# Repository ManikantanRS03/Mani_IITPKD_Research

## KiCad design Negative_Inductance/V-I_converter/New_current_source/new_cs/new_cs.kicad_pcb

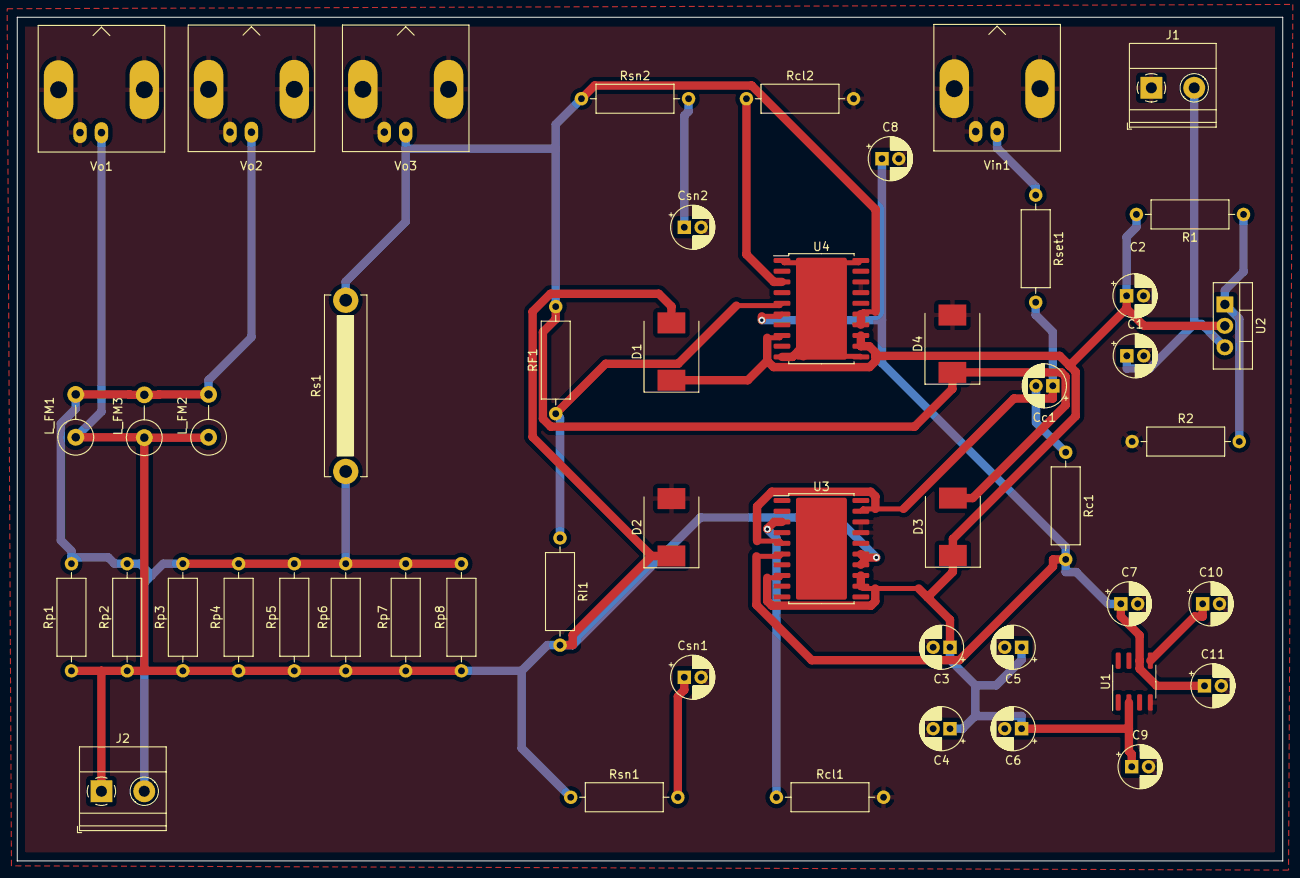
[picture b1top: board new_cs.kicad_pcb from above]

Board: 2 copper layers, 150.0 x 100.0 mm, 50 parts (0 on the bottom side), 17 nets.

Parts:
C1, C2, C4, C6, C11: 47uF; CP_Radial_D5.0mm_P2.00mm
C3, C5, C7, C8: 0.1uF; CP_Radial_D5.0mm_P2.00mm
C9, C10: 1uF; CP_Radial_D5.0mm_P2.00mm
Cc1: 0.47uF; CP_Radial_D5.0mm_P2.00mm
Csn1, Csn2: 0.01uF; CP_Radial_D5.0mm_P2.00mm
D1, D2, D3, D4: 0.35V; D_SMC
J1: +10V; TerminalBlock_Phoenix_MKDS-1,5-2-5.08_1x02_P5.08mm_Horizont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
J2: Iout; TerminalBlock_Phoenix_MKDS-1,5-2-5.08_1x02_P5.08mm_Horizont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
L_FM1, L_FM2, L_FM3: 0.1mH; L_Axial_L9.5mm_D4.0mm_P5.08mm_Vertical_Fastron_SMCC
R1: 240; R_Axial_DIN0309_L9.0mm_D3.2mm_P12.70mm_Horizontal
R2: 720; R_Axial_DIN0309_L9.0mm_D3.2mm_P12.70mm_Horizontal
RF1: 1k; R_Axial_DIN0309_L9.0mm_D3.2mm_P12.70mm_Horizontal
RI1: 1k; R_Axial_DIN0309_L9.0mm_D3.2mm_P12.70mm_Horizontal
Rc1: 249; R_Axial_DIN0309_L9.0mm_D3.2mm_P12.70mm_Horizontal
Rcl1, Rcl2: 5.49k; R_Axial_DIN0309_L9.0mm_D3.2mm_P12.70mm_Horizontal
Rp1, Rp2, Rp3, Rp4, Rp5, Rp6, Rp7, Rp8: 1; R_Axial_DIN0309_L9.0mm_D3.2mm_P12.70mm_Horizontal
Rs1: 4; R_Bare_Metal_Element_L21.3mm_W4.8mm_P20.30mm
Rset1: 475; R_Axial_DIN0309_L9.0mm_D3.2mm_P12.70mm_Horizontal
Rsn1, Rsn2: 10; R_Axial_DIN0309_L9.0mm_D3.2mm_P12.70mm_Horizontal
U1: REF5025AD; SOIC-8_3.9x4.9mm_P1.27mm
U2: LM317_TO-220; TO-220-3_Vertical
U3, U4: OPA569DWP; SO-20-1EP_7.52x12.825mm_P1.27mm_EP6.045x12.09mm_Mask3.56x4.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
Vin1: Input; BNC_Amphenol_B6252HB-NPP3G-50_Horizontal
Vo1, Vo2, Vo3: Output; BNC_Amphenol_B6252HB-NPP3G-50_Horizontal

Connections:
GND: C1.2, C2.2, C3.2, C4.2, C5.2, C6.2, C7.2, C8.2, C9.2, C10.2, C11.2, Csn1.2, Csn2.2, D2.2 (A), D4.2 (A), J1.1, R2.1, Rcl1.2, Rcl2.2, U1.4 (GND), U3.1 (PAD), U3.10 (PAD), U3.11 (PAD), U3.17 (V-), U3.18 (V-), U3.20 (PAD), U3.21 (PAD), U4.17 (V-), U4.18 (V-), Vin1.2 (Ext), Vo1.2 (Ext), Vo2.2 (Ext), Vo3.2 (Ext)
Imon: Cc1.1, Rset1.2, U3.5 (-IN), U3.19 (IMON)
unnamed: C1.1, J1.2, U2.3 (VI)
unnamed: C10.1, U1.5 (Trim/NR)
unnamed: Cc1.2, Rc1.1
unnamed: Csn1.1, Rsn1.2
unnamed: Csn2.1, Rsn2.2
unnamed: R1.1, R2.2, U2.1 (ADJ)
unnamed: Rcl1.1, U3.3 (ISET)
unnamed: Rcl2.1, U4.3 (ISET)
unnamed: Rset1.1, Vin1.1 (In)
unnamed: U4.1 (PAD), U4.10 (PAD), U4.11 (PAD), U4.20 (PAD), U4.21 (PAD)
Vcc: C2.1, C3.1, C4.1, C5.1, C6.1, C9.1, D1.1 (K), D3.1 (K), R1.2, U1.2 (Vin), U2.2 (VO), U3.8 (ENA), U3.12 (V+), U3.13 (V+), U4.8 (ENA), U4.12 (V+), U4.13 (V+)
Vm1: D1.2 (A), D2.1 (K), J2.1, L_FM1.1, L_FM2.1, L_FM3.1, RI1.2, Rp1.1, Rp2.1, Rp3.1, Rp4.1, Rp5.1, Rp6.1, Rp7.1, Rp8.1, Rsn1.1, U3.14 (OUT), U3.15 (OUT), Vo1.1 (In)
Vm2: J2.2, L_FM1.2, L_FM2.2, L_FM3.2, Rp1.2, Rp2.2, Rp3.2, Rp4.2, Rp5.2, Rp6.2, Rp7.2, Rp8.2, Rs1.1, Vo2.1 (In)
Vm3: D3.2 (A), D4.1 (K), RF1.2, Rs1.2, Rsn2.1, U4.14 (OUT), U4.15 (OUT), Vo3.1 (In)
Vref: C7.1, C8.1, C11.1, Rc1.2, U1.6 (Vout), U3.6 (+IN), U4.6 (+IN)

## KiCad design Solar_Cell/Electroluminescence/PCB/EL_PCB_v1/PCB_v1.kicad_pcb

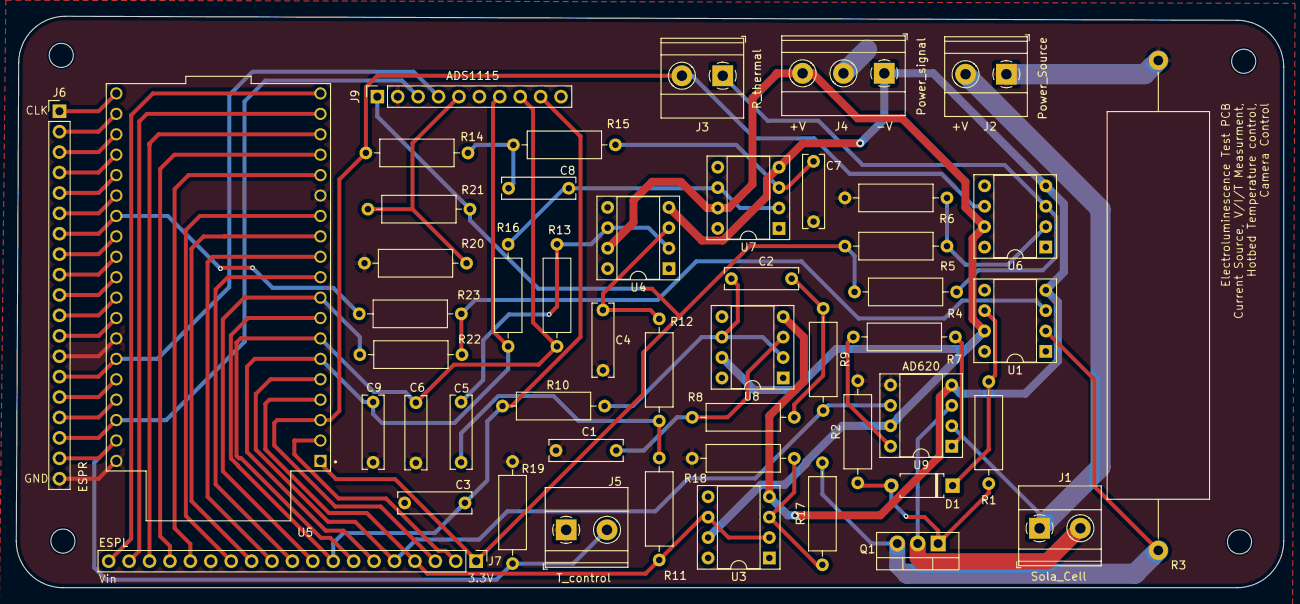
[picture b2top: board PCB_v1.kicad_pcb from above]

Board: 2 copper layers, 157.7 x 71.1 mm, 54 parts (0 on the bottom side), 59 nets.

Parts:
C1, C2, C3, C4, C5, C6, C7, C8, C9: C; C_Rect_L9.0mm_W2.5mm_P7.50mm_MKT
D1: D; D_A-405_P7.62mm_Horizontal
H1, H2, H3, H4: MountingHole; MountingHole_3mm
J1: Sola_Cell; TerminalBlock_Phoenix_MKDS-1,5-2-5.08_1x02_P5.08mm_Horizont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
J2: Power_Source; TerminalBlock_Phoenix_MKDS-1,5-2-5.08_1x02_P5.08mm_Horizont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
J3: R_thermal; TerminalBlock_Phoenix_MKDS-1,5-2-5.08_1x02_P5.08mm_Horizont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
J4: Power_signal; TerminalBlock_Phoenix_MKDS-1,5-3-5.08_1x03_P5.08mm_Horizont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
J5: T_control; TerminalBlock_Phoenix_MKDS-1,5-2-5.08_1x02_P5.08mm_Horizont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
J6: ESPR; PinHeader_1x19_P2.54mm_Vertical
J7: ESPL; PinHeader_1x19_P2.54mm_Vertical
J9: ADS1115; PinSocket_1x10_P2.54mm_Vertical
Q1: IRF540N; TO-220-3_Vertical
R1, R2, R4, R5, R6, R7, R8, R9, R10, R11, R12, R13, R14, R15, R16, R17, R18, R19, R20, R21, R22, R23: R_US; R_Axial_DIN0309_L9.0mm_D3.2mm_P12.70mm_Horizontal
R3: R_US; R_Axial_Power_L48.0mm_W12.5mm_P60.96mm
U1, U3, U4, U6, U7, U8: OP07; DIP-8_W7.62mm_Socket
U5: DEVKIT_V1_ESP32-WROOM-32; MODULE_DEVKIT_V1_ESP32-WROOM-32
U9: AD620; DIP-8_W7.62mm_Socket

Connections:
3.3V: J7.1, J9.1, R4.2, R5.2, R21.2, U5.1 (3V3)
A0: C9.1, J7.6, J9.7, R16.1, U5.6 (IO35)
A1: C6.1, J7.7, J9.8, R13.1, U5.7 (IO32)
A2: C3.1, J7.8, J9.9, R10.1, U5.8 (IO33)
ADDR: J9.5, R20.1, R21.1
DAC1: J7.9, R22.2, U5.9 (IO25)
DAC2: J7.10, U5.10 (IO26)
EN: J7.2, U5.2 (EN)
GND: C1.2, C3.2, C4.2, C6.2, C7.2, C9.2, J2.1, J4.2, J5.1, J6.13, J6.19, J7.14, J9.2, R2.2, R3.2, R6.2, R18.2, R19.2, R20.2, U5.14 (GND1), U5.32 (GND2), U5.38 (GND3), U9.5 (Ref)
GPIO0/ADC11: J6.6, U5.25 (IO0)
GPIO2/ADC12: J6.5, U5.24 (IO2)
GPIO4/ADC10: J6.7, R23.2, U5.26 (IO4)
GPIO5: J6.10, U5.29 (IO5)
GPIO6: J6.1, U5.20 (CLK)
GPIO7: J6.2, U5.21 (SD0)
GPIO8: J6.3, U5.22 (SD1)
GPIO9: J7.16, U5.16 (SD2)
GPIO10: J7.17, U5.17 (SD3)
GPIO11: J7.18, U5.18 (CMD)
GPIO12/ADC15: J7.13, U5.13 (IO12)
GPIO13/ADC14: J7.15, U5.15 (IO13)
GPIO14/ADC16: J7.12, U5.12 (IO14)
GPIO15/ADC13: J6.4, U5.23 (IO15)
GPIO16: J6.8, U5.27 (IO16)
GPIO17: J6.9, U5.28 (IO17)
GPIO18: J6.11, U5.30 (IO18)
GPIO19: J6.12, U5.31 (IO19)
GPIO21: J6.14, J9.4, U5.33 (IO21)
GPIO22: J6.17, J9.3, U5.36 (IO22)
GPIO23: J5.2, J6.18, R19.1, U5.37 (IO23)
GPIO27/ADC17: J7.11, U5.11 (IO27)
GPIO34/ADC6: J7.5, R9.2, U5.5 (IO34), U9.6
GPIO36/ADC0: J3.2, J7.3, R14.2, U5.3 (SENSOR_VP), U6.6
GPIO39/ADC3: J7.4, R11.2, U3.2 (-), U3.6, U5.4 (SENSOR_VN)
I_meas: Q1.3 (S), R3.1, R17.2, U1.2 (-)
I_ref: R22.1, R23.1, U1.3 (+)
unnamed: C2.2, R8.2, R9.1
unnamed: C5.2, R11.1, R12.2
unnamed: C8.2, R14.1, R15.2
unnamed: D1.2 (A), Q1.1 (G), R1.1, R2.1
unnamed: D1.1 (K), R1.2, U1.6
unnamed: R7.1, U9.1 (Rg)
unnamed: R7.2, U9.8 (Rg)
unnamed: R17.1, R18.1, U3.3 (+)
unnamed: C4.1, R12.1, U4.3 (+)
unnamed: C5.1, R13.2, U4.2 (-), U4.6
unnamed: R5.1, R6.1, U6.2 (-)
unnamed: C7.1, R15.1, U7.3 (+)
unnamed: C8.1, R16.2, U7.2 (-), U7.6
unnamed: C1.1, R8.1, U8.3 (+)
unnamed: C2.1, R10.2, U8.2 (-), U8.6
R_T1: J3.1, R4.1, U6.3 (+)
Rx0: J6.15, U5.34 (RXD0)
Tx0: J6.16, U5.35 (TXD0)
VEE: J4.1, U1.4 (V-), U3.4 (V-), U4.4 (V-), U6.4 (V-), U7.4 (V-), U8.4 (V-), U9.4 (Vs-)
VSS: J4.3, U1.7 (V+), U3.7 (V+), U4.7 (V+), U6.7 (V+), U7.7 (V+), U8.7 (V+), U9.7 (Vs+)
V_cell+: J1.1, J2.2, U9.2 (-)
V_cell-: J1.2, Q1.2 (D), U9.3 (+)
Vin: J7.19, U5.19 (EXT_5V)

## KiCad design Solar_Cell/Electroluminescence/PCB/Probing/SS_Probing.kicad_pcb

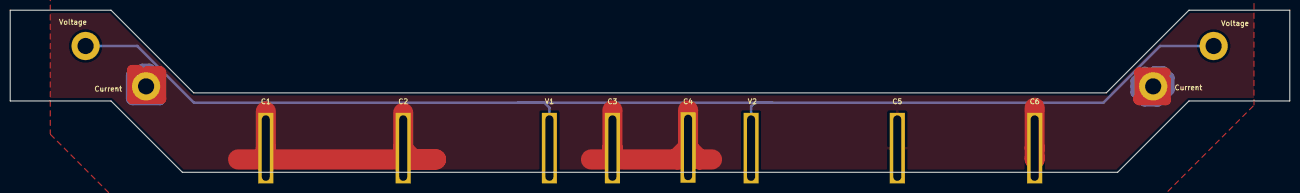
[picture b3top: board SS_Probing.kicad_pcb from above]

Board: 2 copper layers, 253.8 x 32.1 mm, 12 parts (0 on the bottom side), 2 nets.

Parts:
C1, C2, C3, C4, C5, C6: 0.64mm Pogo Pin
Current: Conn_01x02_Socket; MountingHole_3.2mm_M3_DIN965_Pad
Current#2: Conn_01x02_Socket; MountingHole_3.2mm_M3_DIN965_Pad
V1, V2: 0.64mm Pogo Pin
Voltage: Conn_01x02_Socket; MountingHole_3.2mm_M3_DIN965_Pad
Voltage#2: Conn_01x02_Socket; MountingHole_3.2mm_M3_DIN965_Pad

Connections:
Current: C1.1, C2.1, C3.1, C5.1, C6.1, Current.1, Current#2.1, V2.1
Voltage: C4.1, V1.1, Voltage.1, Voltage#2.1

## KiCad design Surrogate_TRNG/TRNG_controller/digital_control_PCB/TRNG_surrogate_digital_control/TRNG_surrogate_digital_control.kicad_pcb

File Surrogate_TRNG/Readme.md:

-> Spice_python_simulation
    . Contains simulation of the surrogate circuit automated through a Python script to generate:
        - Kramers time plots
        - TRNG plots

-> TRNG_controller
    . Contains the BTP work carried out in Sem 7/8. Modified the surrogate circuit to incorporate a        
    digital control mechanism (details of implementation in the report provided)
        - PCB design (KiCad)
        - Measurements done on the setup (more details in the README inside)
        - Noise generation code for the Innovation Lab function generator
        - MATLAB/Simulink simulations to test the control design

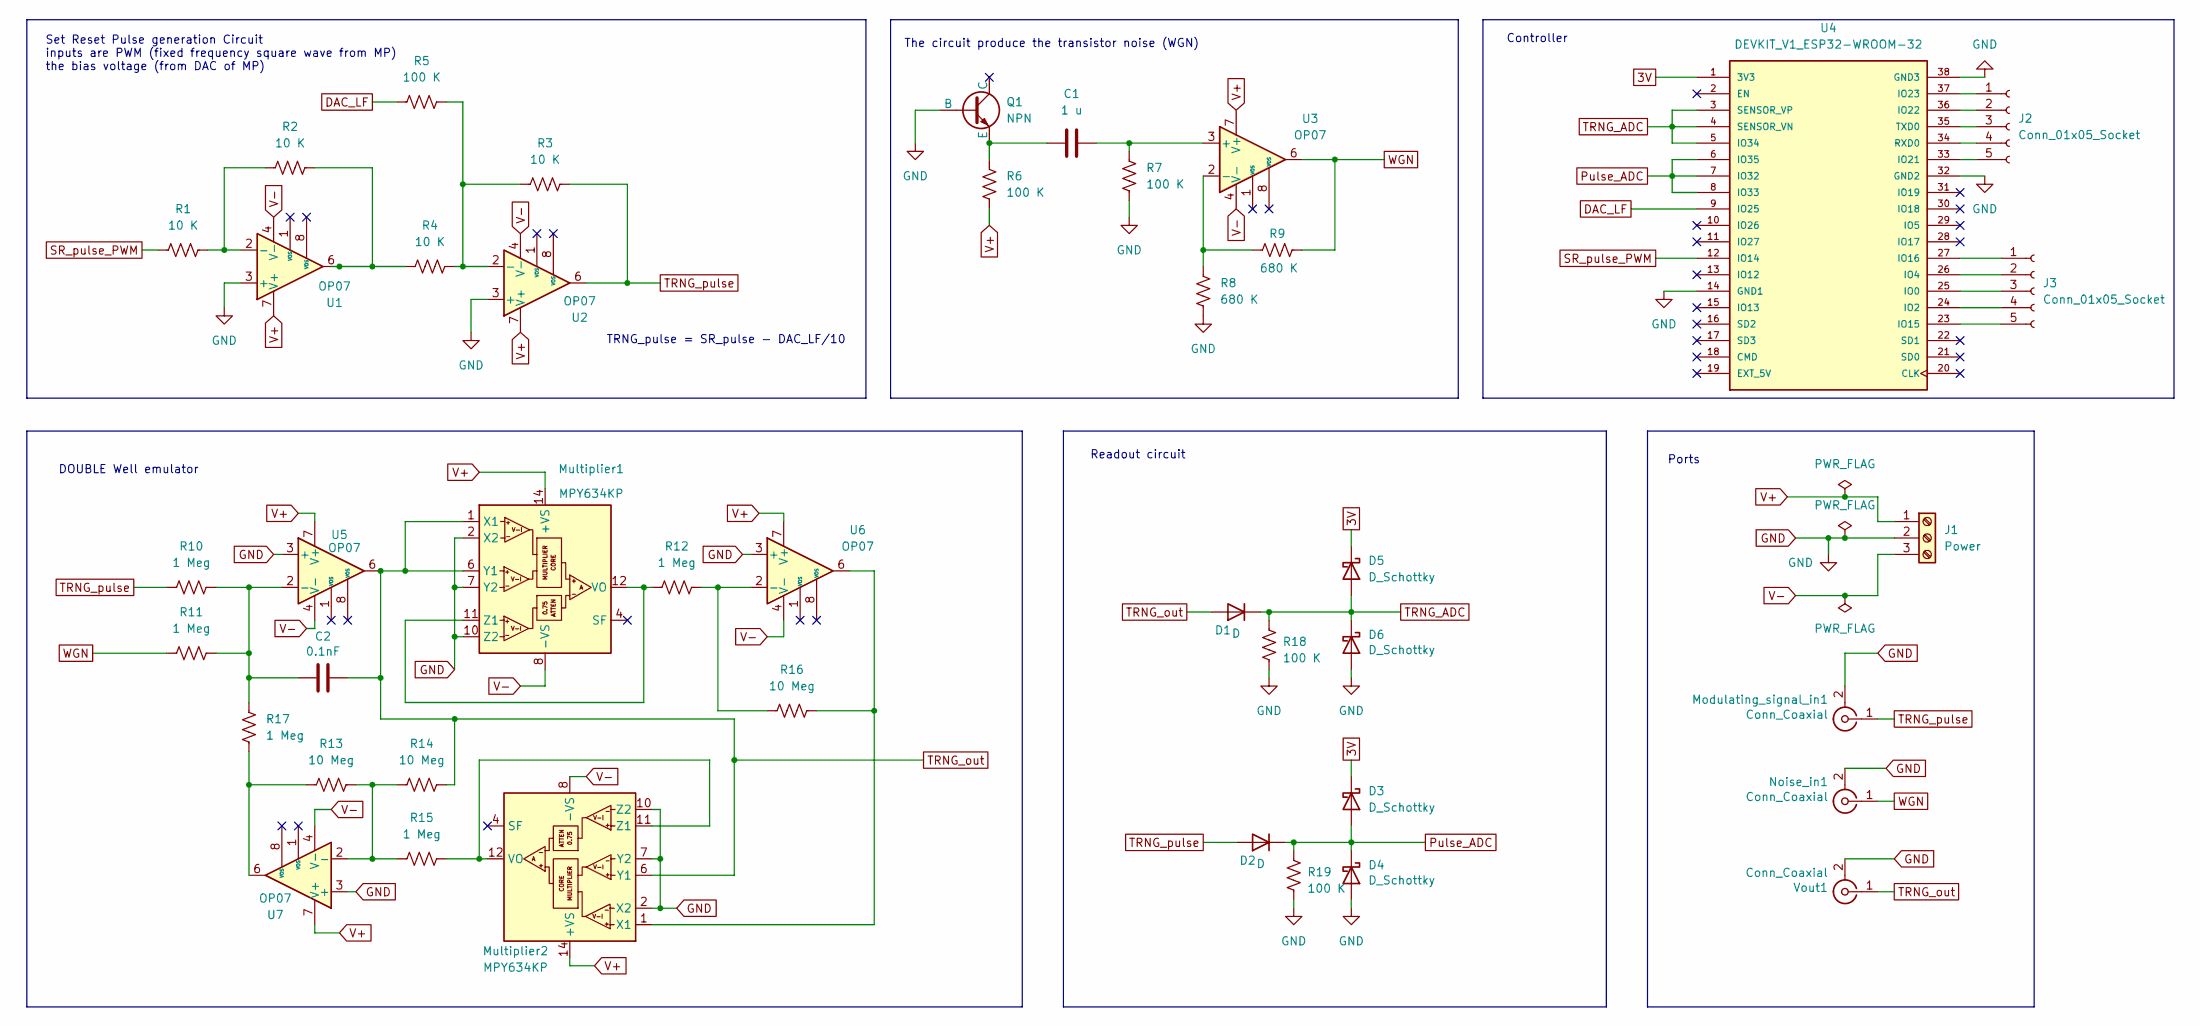
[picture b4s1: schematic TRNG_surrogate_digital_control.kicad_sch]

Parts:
C1: 1 u; C_Rect_L9.0mm_W2.5mm_P7.50mm_MKT
C2: 0.1nF; C_Rect_L9.0mm_W2.5mm_P7.50mm_MKT
D1, D2: D; D_A-405_P7.62mm_Horizontal
D3, D4, D5, D6: D_Schottky; D_A-405_P7.62mm_Horizontal
J1: Power; TerminalBlock_Phoenix_MKDS-3-3-5.08_1x03_P5.08mm_Horizontal
J2, J3: Conn_01x05_Socket; PinSocket_1x05_P2.54mm_Vertical
Modulating_signal_in1: Conn_Coaxial; BNC_Amphenol_B6252HB-NPP3G-50_Horizontal
Multiplier1, Multiplier2: MPY634KP; DIP-14_W7.62mm_Socket
Noise_in1: Conn_Coaxial; BNC_Amphenol_B6252HB-NPP3G-50_Horizontal
Q1: NPN; TO-92
R1, R2, R3, R4: 10 K; R_Axial_DIN0309_L9.0mm_D3.2mm_P12.70mm_Horizontal
R5, R6, R7, R18, R19: 100 K; R_Axial_DIN0309_L9.0mm_D3.2mm_P12.70mm_Horizontal
R8, R9: 680 K; R_Axial_DIN0309_L9.0mm_D3.2mm_P12.70mm_Horizontal
R10, R11, R12, R15, R17: 1 Meg; R_Axial_DIN0309_L9.0mm_D3.2mm_P12.70mm_Horizontal
R13, R14, R16: 10 Meg; R_Axial_DIN0309_L9.0mm_D3.2mm_P12.70mm_Horizontal
U1, U2, U3, U5, U6, U7: OP07; DIP-8_W7.62mm_Socket
U4: DEVKIT_V1_ESP32-WROOM-32; MODULE_DEVKIT_V1_ESP32-WROOM-32; PARTREV N/A
Vout1: Conn_Coaxial; BNC_Amphenol_B6252HB-NPP3G-50_Horizontal

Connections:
3V: D3.1 (K), D5.1 (K), U4.1 (3V3)
DAC_LF: R5.1, U4.9 (IO25)
GND: D4.2 (A), D6.2 (A), J1.2, Modulating_signal_in1.2 (Ext), Multiplier1.2 (X2), Multiplier1.7 (Y2), Multiplier1.10 (Z2), Multiplier2.2 (X2), Multiplier2.7 (Y2), Multiplier2.10 (Z2), Noise_in1.2 (Ext), Q1.2 (B), R7.1, R8.1, R18.1, R19.1, U1.3 (+), U2.3 (+), U4.14 (GND1), U4.32 (GND2), U4.38 (GND3), U5.3 (+), U6.3 (+), U7.3 (+), Vout1.2 (Ext)
unnamed: J2.1, U4.37 (IO23)
unnamed: J2.2, U4.36 (IO22)
unnamed: J2.3, U4.35 (TXD0)
unnamed: J2.4, U4.34 (RXD0)
unnamed: J2.5, U4.33 (IO21)
unnamed: J3.1, U4.27 (IO16)
unnamed: J3.2, U4.26 (IO4)
unnamed: J3.3, U4.25 (IO0)
unnamed: J3.4, U4.24 (IO2)
unnamed: J3.5, U4.23 (IO15)
unnamed: Multiplier1.11 (Z1), Multiplier1.12 (VO), R12.1
unnamed: Multiplier2.11 (Z1), Multiplier2.12 (VO), R15.2
unnamed: Multiplier2.1 (X1), R16.2, U6.6
unnamed: C1.1, Q1.3 (E), R6.2
unnamed: R2.2, R4.1, U1.6
unnamed: R13.1, R17.1, U7.6
unnamed: R1.2, R2.1, U1.2 (-)
unnamed: R3.1, R4.2, R5.2, U2.2 (-)
unnamed: C1.2, R7.2, U3.3 (+)
unnamed: R8.2, R9.2, U3.2 (-)
unnamed: C2.2, R10.2, R11.2, R17.2, U5.2 (-)
unnamed: R12.2, R16.1, U6.2 (-)
unnamed: R13.2, R14.1, R15.1, U7.2 (-)
Pulse_ADC: D2.1 (K), D3.2 (A), D4.1 (K), R19.2, U4.6 (IO35), U4.7 (IO32), U4.8 (IO33)
SR_pulse_PWM: R1.1, U4.12 (IO14)
TRNG_ADC: D1.1 (K), D5.2 (A), D6.1 (K), R18.2, U4.3 (SENSOR_VP), U4.4 (SENSOR_VN), U4.5 (IO34)
TRNG_out: C2.1, D1.2 (A), Multiplier1.1 (X1), Multiplier1.6 (Y1), Multiplier2.6 (Y1), R14.2, U5.6, Vout1.1 (In)
TRNG_pulse: D2.2 (A), Modulating_signal_in1.1 (In), R3.2, R10.1, U2.6
V+: J1.1, Multiplier1.14 (+VS), Multiplier2.14 (+VS), R6.1, U1.7 (V+), U2.7 (V+), U3.7 (V+), U5.7 (V+), U6.7 (V+), U7.7 (V+)
V-: J1.3, Multiplier1.8 (-VS), Multiplier2.8 (-VS), U1.4 (V-), U2.4 (V-), U3.4 (V-), U5.4 (V-), U6.4 (V-), U7.4 (V-)
WGN: Noise_in1.1 (In), R9.1, R11.1, U3.6

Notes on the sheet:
DOUBLE Well emulator
Set Reset Pulse generation Circuit inputs are PWM (fixed frequency square wave from MP) the bias voltage (from DAC of MP)
Ports
Readout circuit
TRNG_pulse = SR_pulse - DAC_LF/10
Controller
The circuit produce the transistor noise (WGN)

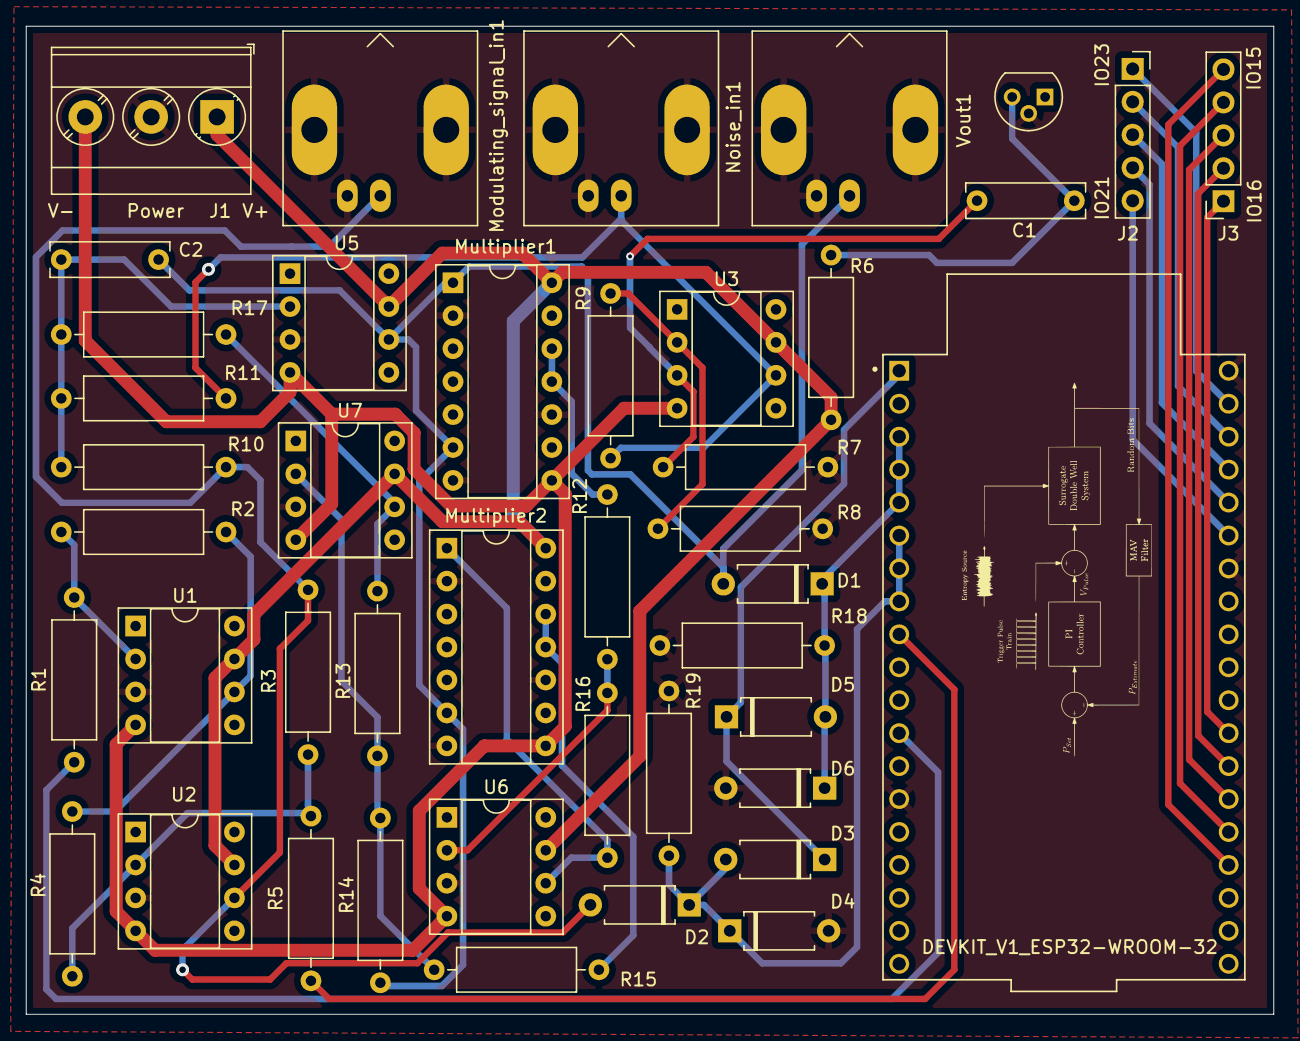
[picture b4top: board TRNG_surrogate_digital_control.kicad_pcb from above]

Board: 2 copper layers, 96.2 x 76.2 mm, 43 parts (0 on the bottom side), 34 nets.

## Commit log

2025-08-03 Research repository first commit
2025-08-03 solar cell added
2025-08-03 NI added
2025-08-24 TRNG paper figures added
2025-09-27 trng paper updates
2025-12-11 FE-SR paper review 1, rework
